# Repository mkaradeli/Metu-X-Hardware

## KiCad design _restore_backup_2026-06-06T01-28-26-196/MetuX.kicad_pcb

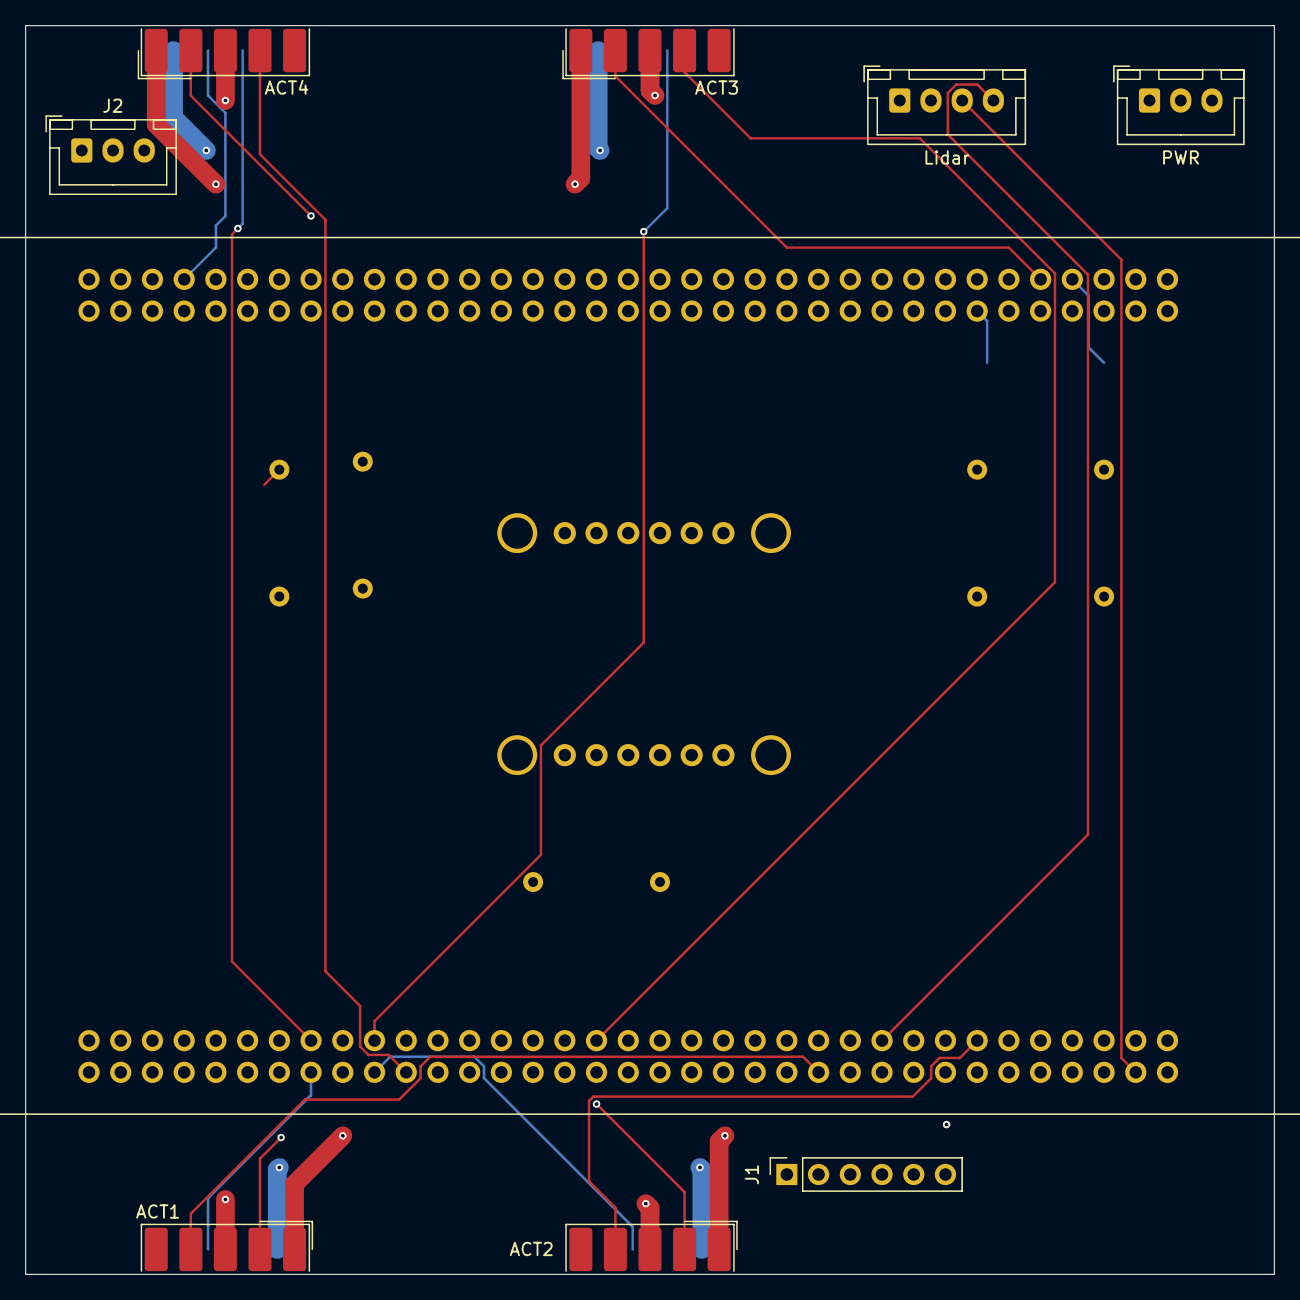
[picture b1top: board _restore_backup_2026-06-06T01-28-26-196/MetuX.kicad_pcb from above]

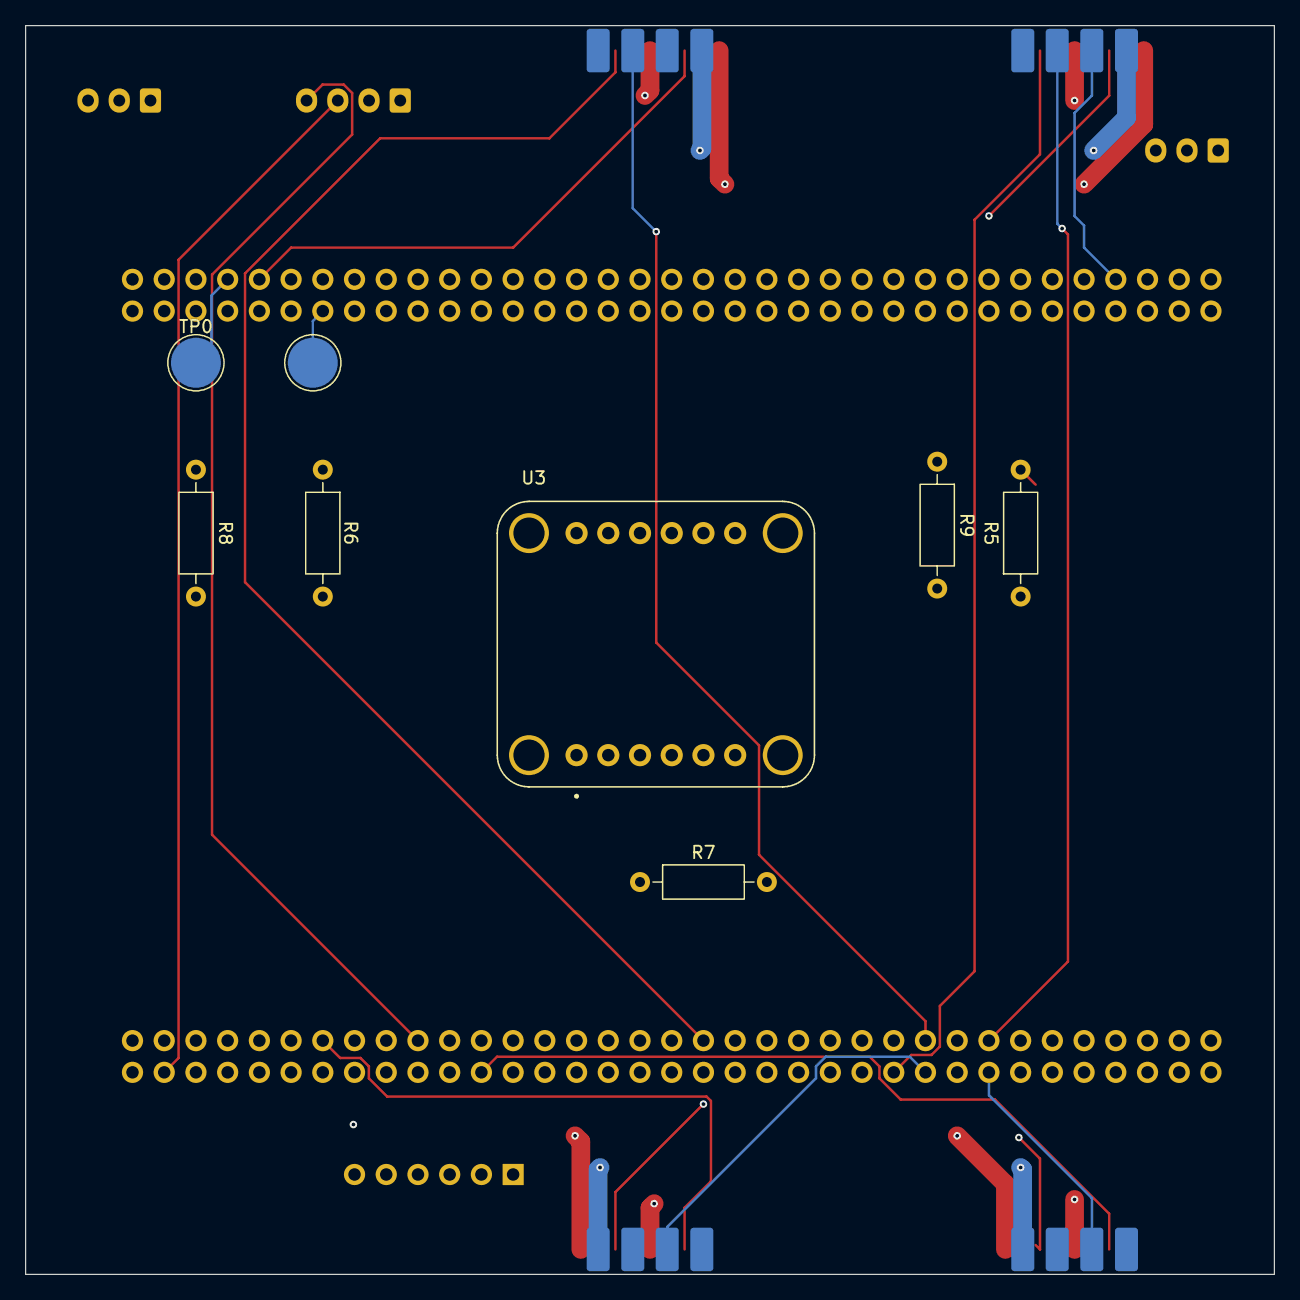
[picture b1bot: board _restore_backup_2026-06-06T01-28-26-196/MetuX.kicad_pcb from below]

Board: 4 copper layers, 100.0 x 100.0 mm, 17 parts (8 on the bottom side), 38 nets.

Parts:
ACT1, ACT2, ACT3, ACT4: DE9_Socket; DSUB-9_Socket_EdgeMount_P2.77mm
J1: SD_Card_Breakout; PinSocket_1x06_P2.54mm_Vertical
J2: Manifold; JST_XH_B3B-XH-A_1x03_P2.50mm_Vertical
J3: PWR; JST_XH_B3B-XH-A_1x03_P2.50mm_Vertical
J4: Lidar; JST_XH_B4B-XH-A_1x04_P2.50mm_Vertical
R5, R6, R7, R8, R9: 150R; R_Axial_DIN0207_L6.3mm_D2.5mm_P10.16mm_Horizontal
TP0: ~{BOOT0}; TestPoint_Pad_D4.0mm
TP1: NRST; TestPoint_Pad_D4.0mm
U2: NUCLEO144-H755ZI-Q
U3: 4754; MODULE_4754

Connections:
+5V: ACT1.1, ACT2.1, ACT3.1, ACT4.1, J1.5 (VCC), J3.1, J4.2, U2.CN11_6 (E5V), U3.JP1_1 (VIN)
+12V: ACT1.6, ACT2.6, ACT3.6, ACT4.6, J2.3, J3.3
/CS0: ACT1.4, U2.CN12_24 (PB1)
/CS1: ACT2.4, U2.CN12_13 (PA6)
/CS2: ACT3.4, U2.CN12_37 (PA3)
/CS3: ACT4.4, U2.CN12_50 (PF14)
/HE0: ACT1.5, U2.CN11_38 (PC0)
/HE1: ACT2.5, U2.CN11_32 (PA4)
/HE2: ACT3.5, U2.CN11_28 (PA0)
/HE3: ACT4.5, U2.CN12_11 (PA5)
/IMU_SCL: U2.CN12_17 (PB6), U3.JP1_4 (SCL)
/IMU_SDA: U2.CN11_21 (LD2/PB7), U3.JP1_5 (SDA)
/LIDAR_UART_RX: J4.4, U2.CN12_19 (PC7)
/LIDAR_UART_TX: J4.3, U2.CN12_4 (PC6)
/L_EN_0: ACT1.9, U2.CN12_47 (PE10)
/L_EN_1: ACT2.9, U2.CN12_53 (PE15)
/L_EN_2: ACT3.9, U2.CN12_18 (PB11)
/L_EN_3: ACT4.9, U2.CN12_44 (PE7)
/PT0: ACT1.2, R5.2, U2.CN11_56 (PF9)
/PT1: ACT2.2, R7.2, U2.CN12_42 (PF10)
/PT2: ACT3.2, R8.1, U2.CN11_9 (PF6)
/PT3: ACT4.2, R6.1, U2.CN11_11 (PF7)
/PT4: J2.1, R9.1, U2.CN11_54 (PF8)
/PWM_0: ACT1.8, U2.CN12_56 (PE11)
/PWM_1: ACT2.8, U2.CN12_52 (PE9)
/PWM_2: ACT3.8, U2.CN12_51 (PE14)
/PWM_3: ACT4.8, U2.CN12_55 (PE13)
/R_EN_0: ACT1.7, U2.CN12_49 (PE12)
/R_EN_1: ACT2.7, U2.CN12_60 (PF15)
/R_EN_2: ACT3.7, U2.CN12_40 (PE8)
/R_EN_3: ACT4.7, U2.CN11_63 (PG9)
/SD_CS: J1.1 (CS), U2.CN12_25 (PB10)
/SD_MISO: J1.4 (MISO), U2.CN12_27 (PB4)
/SD_MOSI: J1.3 (MOSI), U2.CN12_29 (PB5)
/SD_SCK: J1.2 (SCK), U2.CN12_31 (SWO/PB3)
GND: ACT1.3, ACT2.3, ACT3.3, ACT4.3, J1.6 (GND), J3.2, J4.1, R5.1, R6.2, R7.1, R8.2, R9.2, U2.CN11_8 (GND), U2.CN11_19 (GND), U2.CN11_20 (GND), U2.CN11_22 (GND), U2.CN11_49 (GND), U2.CN11_60 (GND), U2.CN12_9 (GND), U2.CN12_20 (GND), U2.CN12_32 (AGND), U2.CN12_39 (GND), U2.CN12_54 (GND), U2.CN12_63 (GND), U3.JP1_3 (GND)
unnamed: TP0.1 (1_1), U2.CN11_7 (~BOOT0)
unnamed: TP1.1 (1_1), U2.CN11_14 (~RST)

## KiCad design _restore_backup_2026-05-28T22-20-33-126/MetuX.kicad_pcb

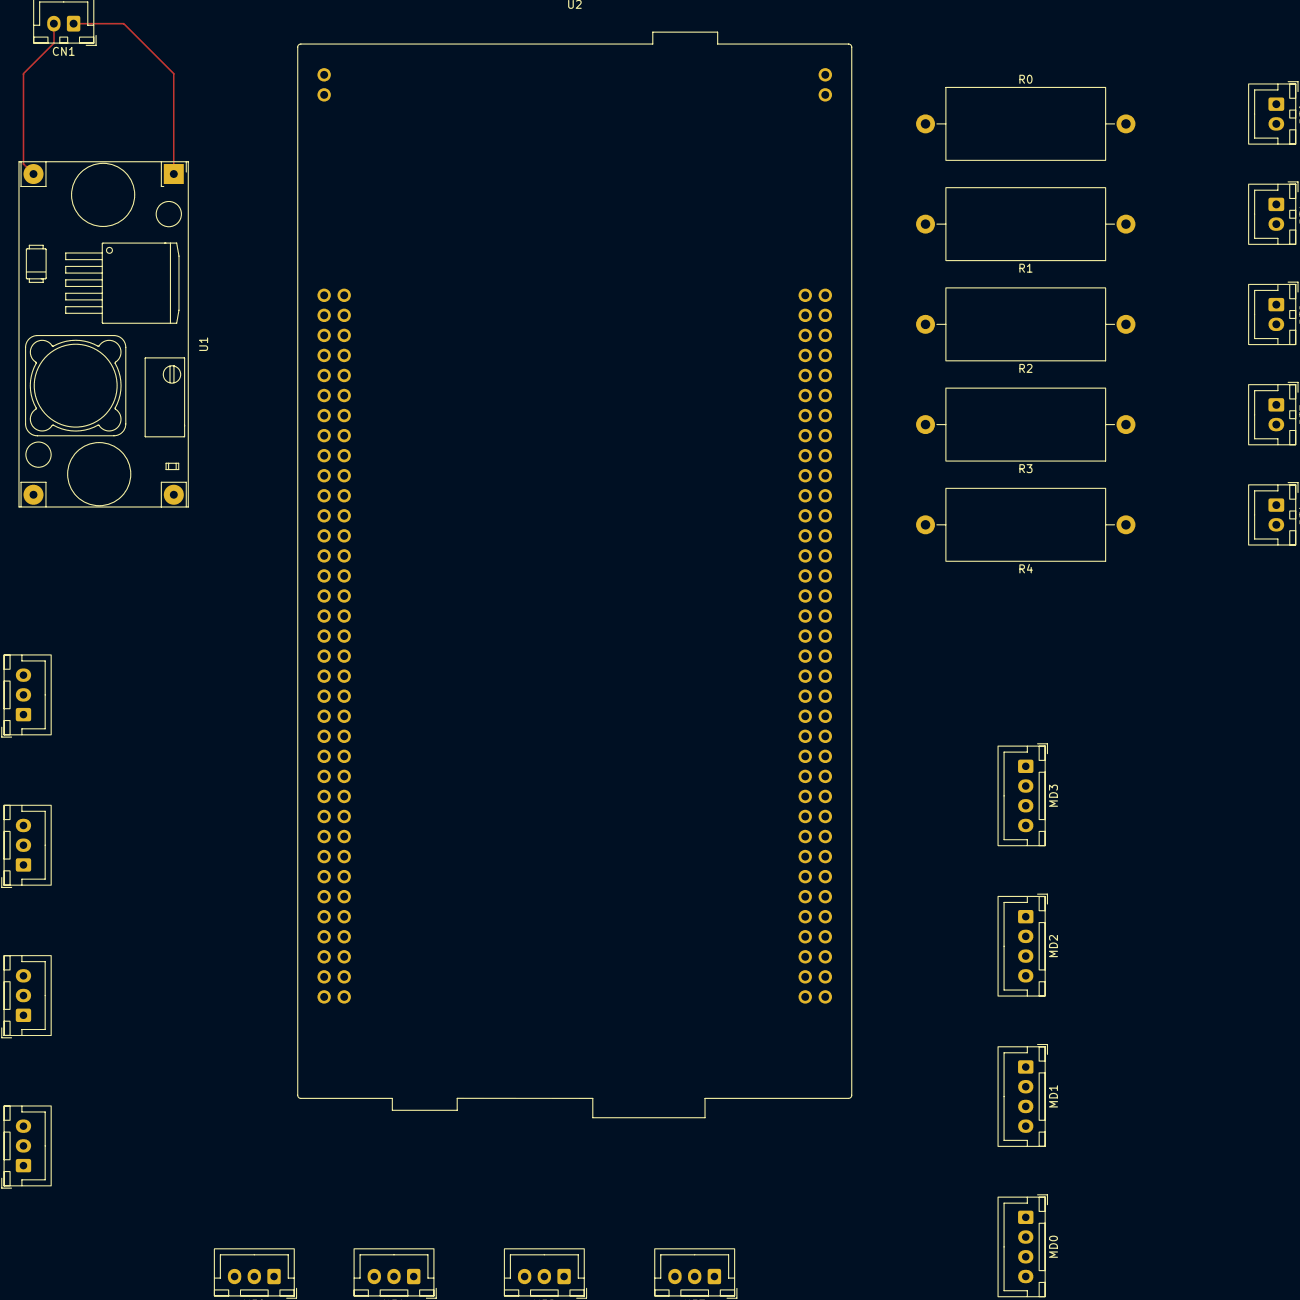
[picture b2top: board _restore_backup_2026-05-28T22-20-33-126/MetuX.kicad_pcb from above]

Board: 2 copper layers, 25 parts (0 on the bottom side), 8 nets.

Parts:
CN1: Conn_01x02_Socket; JST_XH_B2B-XH-A_1x02_P2.50mm_Vertical
CS0, CS1, CS2, CS3: Conn_01x03_Socket; JST_XH_B3B-XH-A_1x03_P2.50mm_Vertical
HE0, HE1, HE2, HE3: Conn_01x03_Socket; JST_XH_B3B-XH-A_1x03_P2.50mm_Vertical
MD0, MD1, MD2, MD3: Conn_01x04_Socket; JST_XH_B4B-XH-A_1x04_P2.50mm_Vertical
PT0, PT1, PT2, PT3, PT4: Conn_01x02_Socket; JST_XH_B2B-XH-A_1x02_P2.50mm_Vertical
R0, R1, R2, R3, R4: 150R; R_Axial_DIN0922_L20.0mm_D9.0mm_P25.40mm_Horizontal
U1: YAAJ_DCDC_StepDown_LM2596
U2: NUCLEO144-H743ZI; ST_Morpho_Connector_144_STLink

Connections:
+5V: CS0.1, CS1.1, CS2.1, CS3.1, HE0.1, HE1.1, HE2.1, HE3.1, U1.4 (Vout)
+12V: CN1.1, PT0.1, PT1.1, PT2.1, PT3.1, PT4.1, U1.1 (Vin)
/Basınç Sensörleri/PT0: PT0.2, R0.2
/Basınç Sensörleri/PT1: PT1.2, R1.1
/Basınç Sensörleri/PT2: PT2.2, R2.1
/Basınç Sensörleri/PT3: PT3.2, R3.1
/Basınç Sensörleri/PT4: PT4.2, R4.1
GND: CN1.2, CS0.3, CS1.3, CS2.3, CS3.3, HE0.3, HE1.3, HE2.3, HE3.3, MD0.1, MD1.1, MD2.1, MD3.1, R0.1, R1.2, R2.2, R3.2, R4.2, U1.2 (GND), U1.3 (GND), U2.19 (GND_19)

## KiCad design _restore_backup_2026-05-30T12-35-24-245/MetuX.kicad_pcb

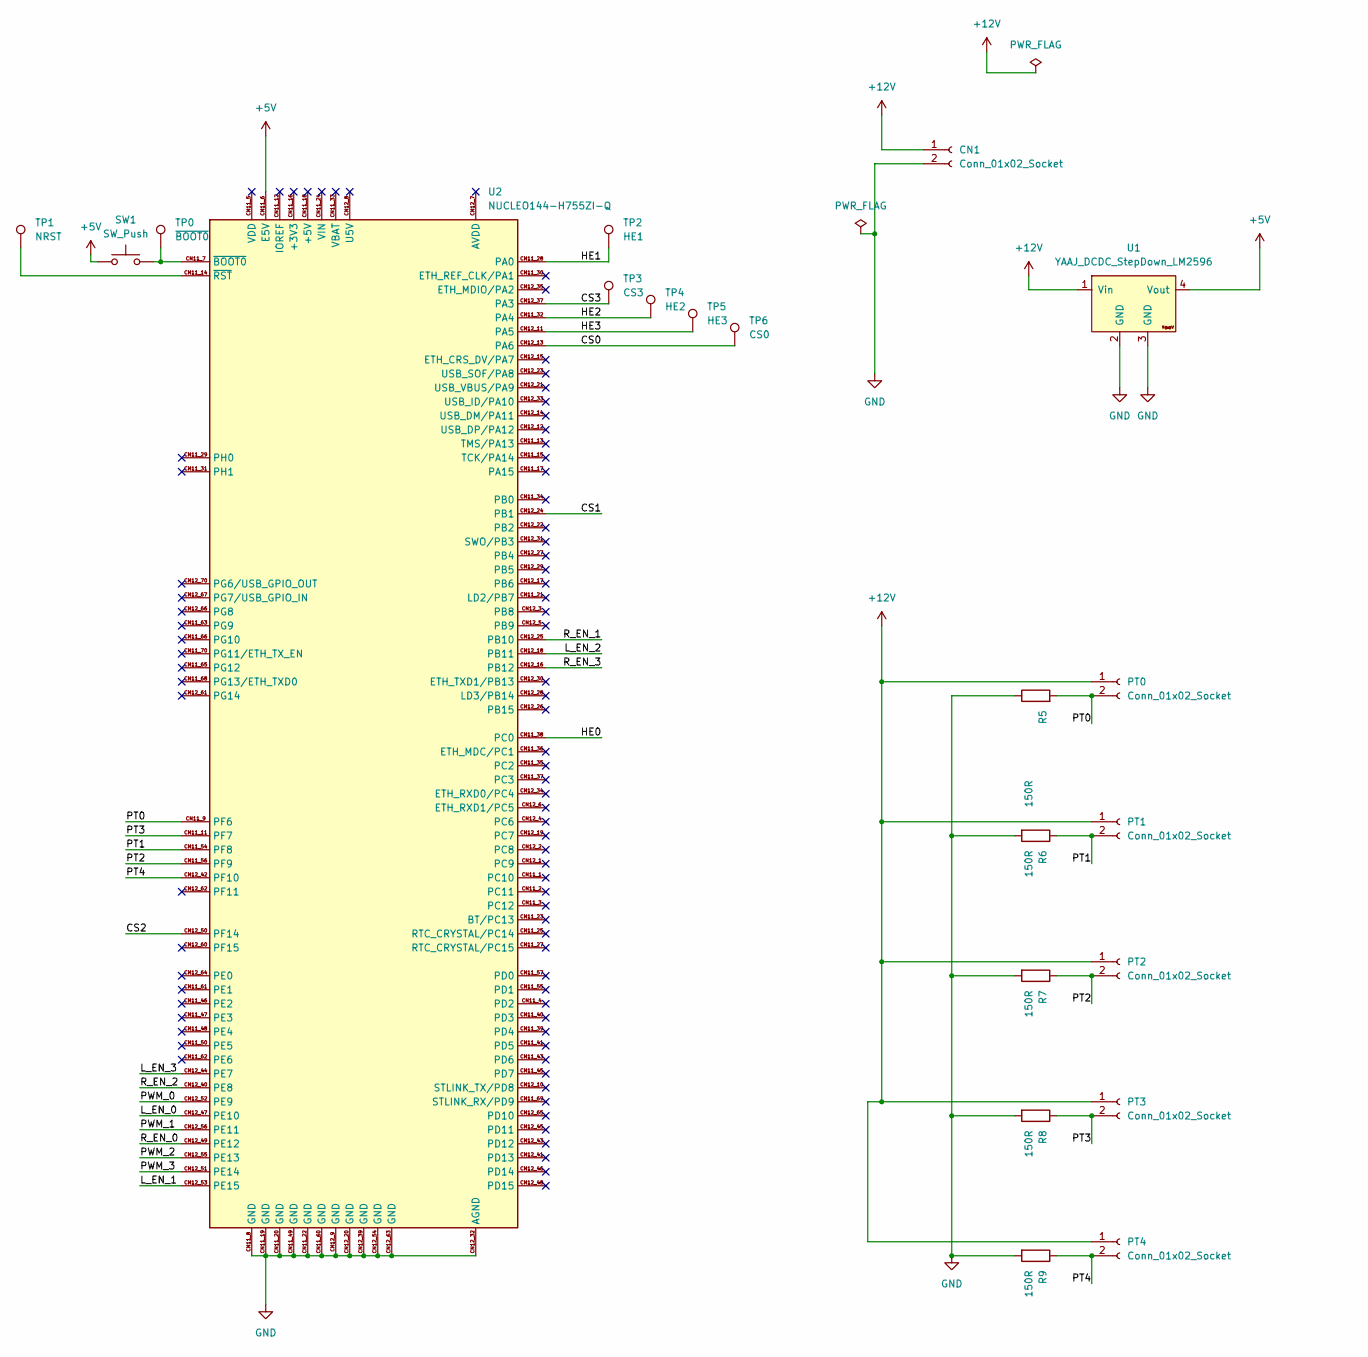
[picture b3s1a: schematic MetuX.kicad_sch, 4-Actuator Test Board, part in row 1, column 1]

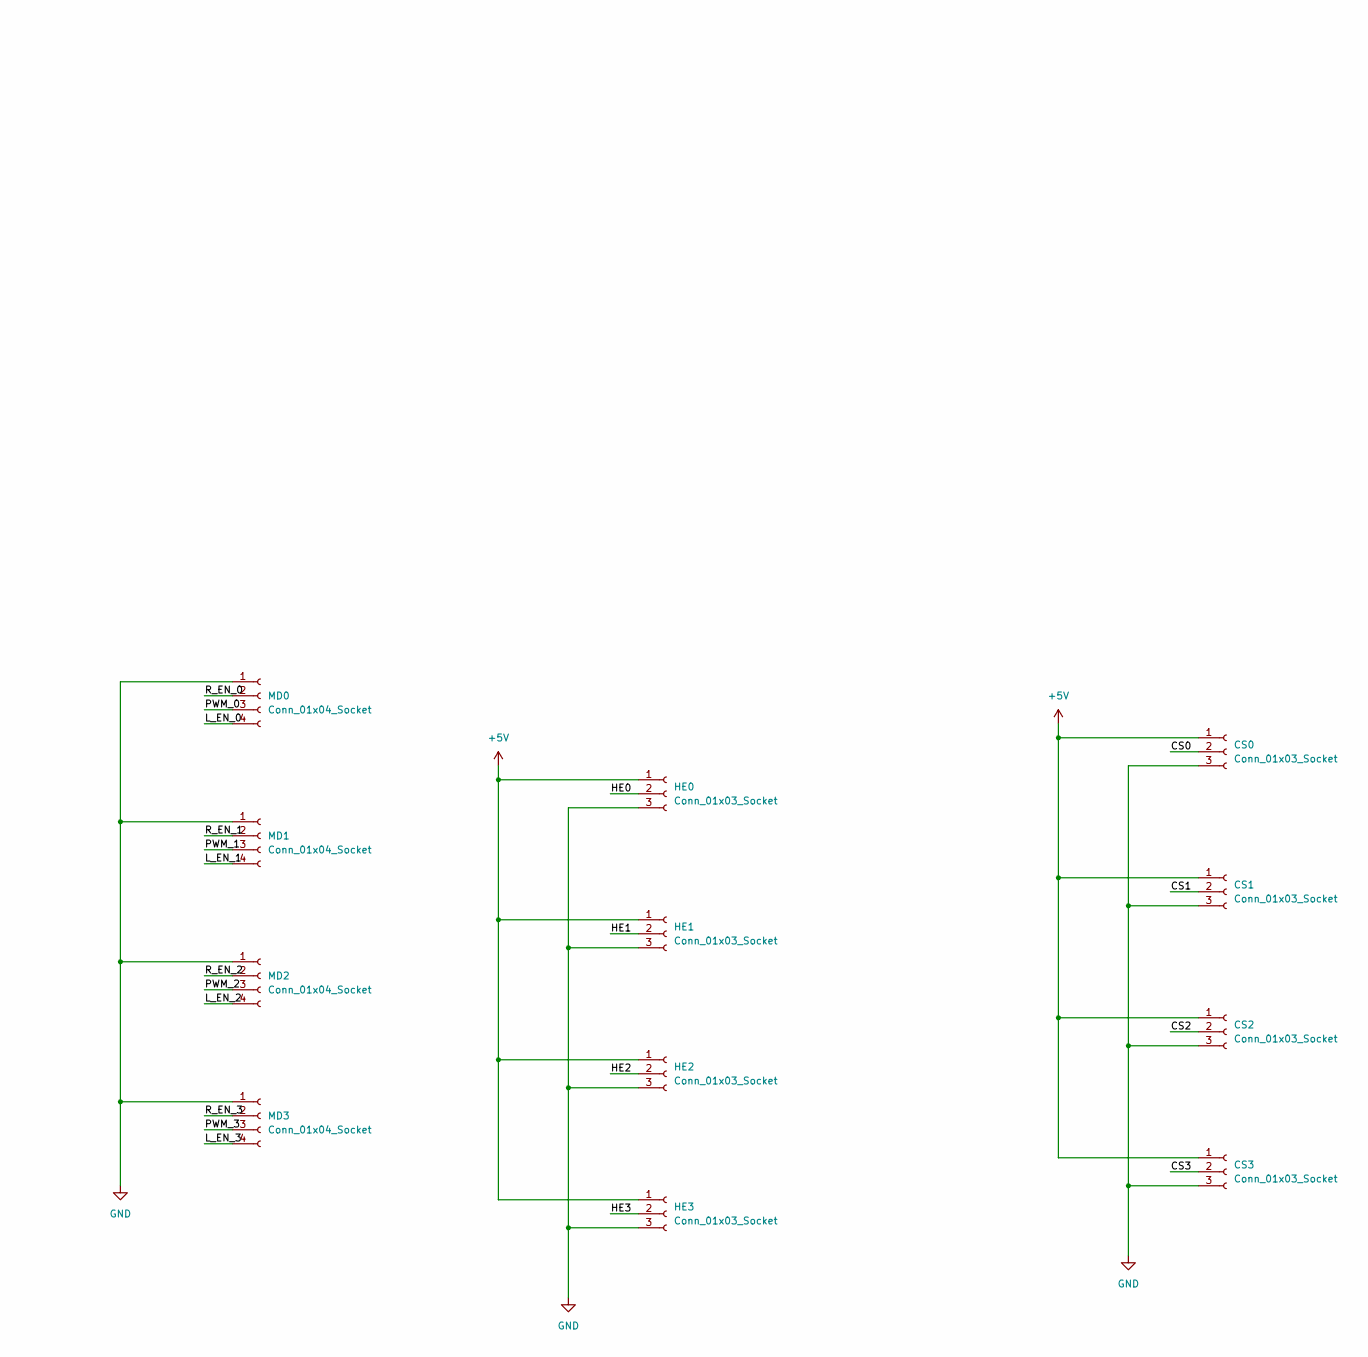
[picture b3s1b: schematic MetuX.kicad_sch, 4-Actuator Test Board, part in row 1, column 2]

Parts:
CN1: Conn_01x02_Socket; JST_XH_B2B-XH-A_1x02_P2.50mm_Vertical
CS0, CS1, CS2, CS3: Conn_01x03_Socket; JST_XH_B3B-XH-A_1x03_P2.50mm_Vertical
HE0, HE1, HE2, HE3: Conn_01x03_Socket; JST_XH_B3B-XH-A_1x03_P2.50mm_Vertical
MD0, MD1, MD2, MD3: Conn_01x04_Socket; JST_XH_B4B-XH-A_1x04_P2.50mm_Vertical
PT0, PT1, PT2, PT3, PT4: Conn_01x02_Socket; JST_XH_B2B-XH-A_1x02_P2.50mm_Vertical
R5, R6, R7, R8, R9: 150R; R_Axial_DIN0207_L6.3mm_D2.5mm_P10.16mm_Horizontal
SW1: SW_Push; SW_PUSH_6mm_H4.3mm
TP0: ~{BOOT0}; TestPoint_Pad_D4.0mm
TP1: NRST; TestPoint_Pad_D4.0mm
TP2: HE1; TestPoint_Pad_D4.0mm
TP3: CS3; TestPoint_Pad_D4.0mm
TP4: HE2; TestPoint_Pad_D4.0mm
TP5: HE3; TestPoint_Pad_D4.0mm
TP6: CS0; TestPoint_Pad_D4.0mm
U1: YAAJ_DCDC_StepDown_LM2596
U2: NUCLEO144-H755ZI-Q

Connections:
+5V: CS0.1, CS1.1, CS2.1, CS3.1, HE0.1, HE1.1, HE2.1, HE3.1, SW1.1, U1.4 (Vout), U2.CN11_6 (E5V)
+12V: CN1.1, PT0.1, PT1.1, PT2.1, PT3.1, PT4.1, U1.1 (Vin)
/CS0: CS0.2, TP6.1 (1_1), U2.CN12_13 (PA6)
/CS1: CS1.2, U2.CN12_24 (PB1)
/CS2: CS2.2, U2.CN12_50 (PF14)
/CS3: CS3.2, TP3.1 (1_1), U2.CN12_37 (PA3)
/HE0: HE0.2, U2.CN11_38 (PC0)
/HE1: HE1.2, TP2.1 (1_1), U2.CN11_28 (PA0)
/HE2: HE2.2, TP4.1 (1_1), U2.CN11_32 (PA4)
/HE3: HE3.2, TP5.1 (1_1), U2.CN12_11 (PA5)
/L_EN_0: MD0.4, U2.CN12_47 (PE10)
/L_EN_1: MD1.4, U2.CN12_53 (PE15)
/L_EN_2: MD2.4, U2.CN12_18 (PB11)
/L_EN_3: MD3.4, U2.CN12_44 (PE7)
/PT0: PT0.2, R5.2, U2.CN11_9 (PF6)
/PT1: PT1.2, R6.1, U2.CN11_54 (PF8)
/PT2: PT2.2, R7.1, U2.CN11_56 (PF9)
/PT3: PT3.2, R8.1, U2.CN11_11 (PF7)
/PT4: PT4.2, R9.1, U2.CN12_42 (PF10)
/PWM_0: MD0.3, U2.CN12_52 (PE9)
/PWM_1: MD1.3, U2.CN12_56 (PE11)
/PWM_2: MD2.3, U2.CN12_55 (PE13)
/PWM_3: MD3.3, U2.CN12_51 (PE14)
/R_EN_0: MD0.2, U2.CN12_49 (PE12)
/R_EN_1: MD1.2, U2.CN12_25 (PB10)
/R_EN_2: MD2.2, U2.CN12_40 (PE8)
/R_EN_3: MD3.2, U2.CN12_16 (PB12)
GND: CN1.2, CS0.3, CS1.3, CS2.3, CS3.3, HE0.3, HE1.3, HE2.3, HE3.3, MD0.1, MD1.1, MD2.1, MD3.1, R5.1, R6.2, R7.2, R8.2, R9.2, U1.2 (GND), U1.3 (GND), U2.CN11_8 (GND), U2.CN11_19 (GND), U2.CN11_20 (GND), U2.CN11_22 (GND), U2.CN11_49 (GND), U2.CN11_60 (GND), U2.CN12_9 (GND), U2.CN12_20 (GND), U2.CN12_32 (AGND), U2.CN12_39 (GND), U2.CN12_54 (GND), U2.CN12_63 (GND)
unnamed: SW1.2, TP0.1 (1_1), U2.CN11_7 (~BOOT0)
unnamed: TP1.1 (1_1), U2.CN11_14 (~RST)

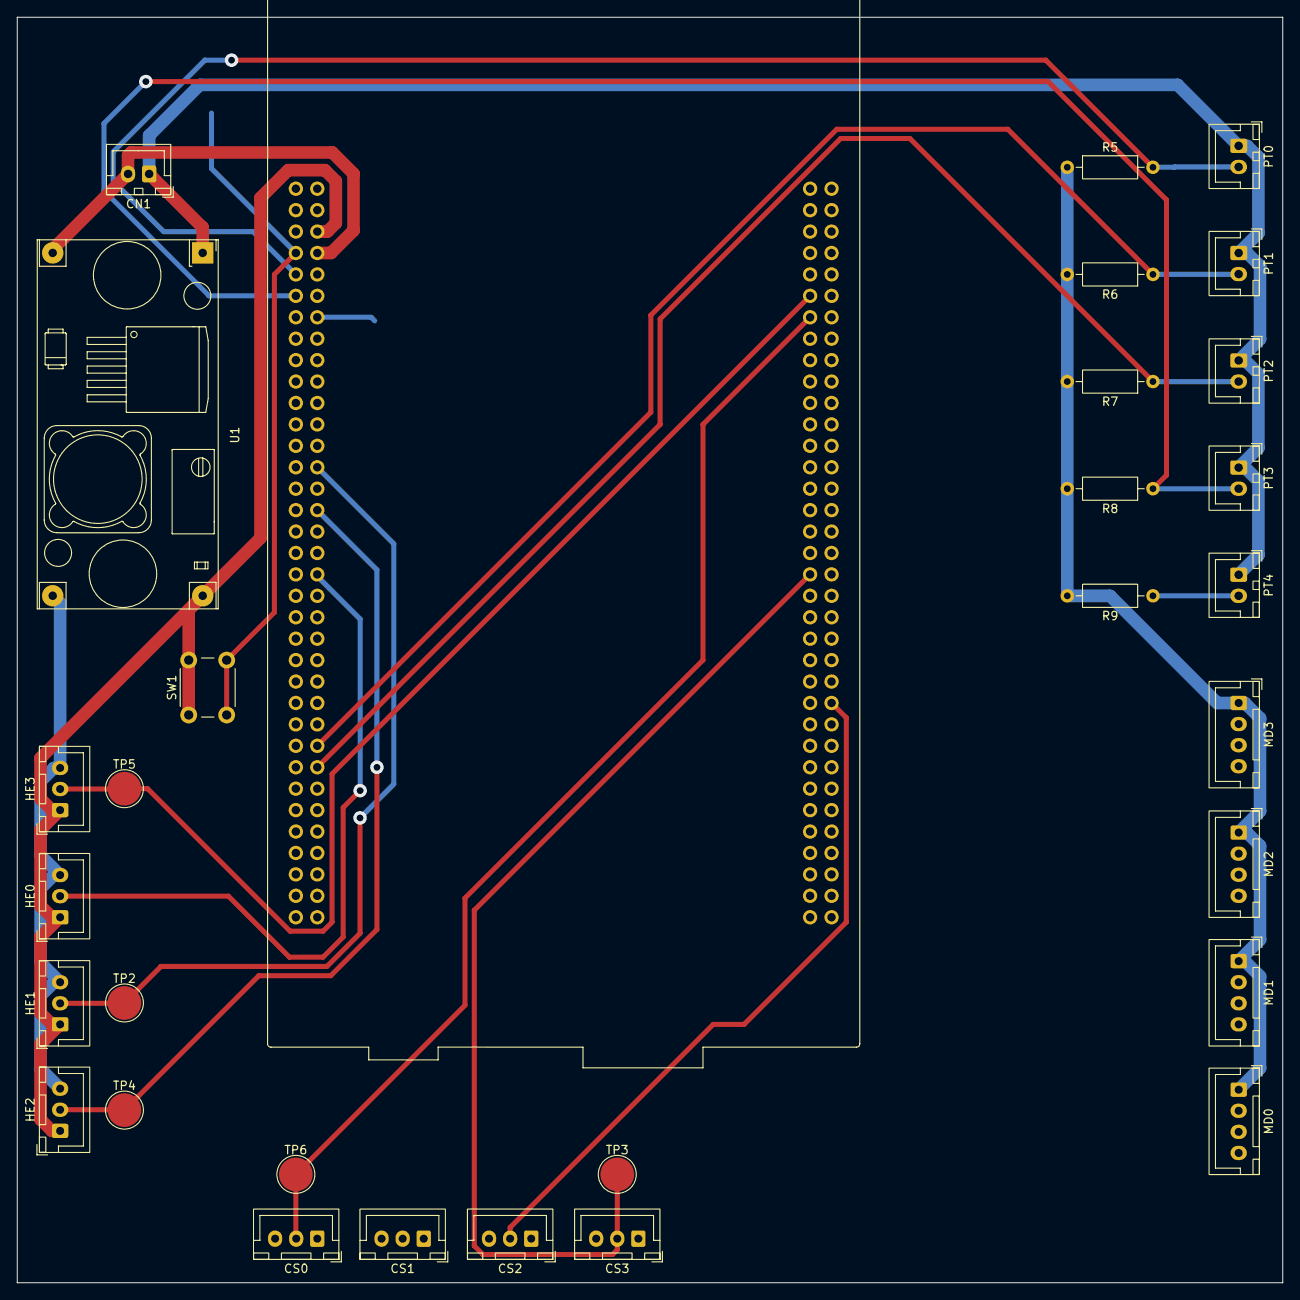
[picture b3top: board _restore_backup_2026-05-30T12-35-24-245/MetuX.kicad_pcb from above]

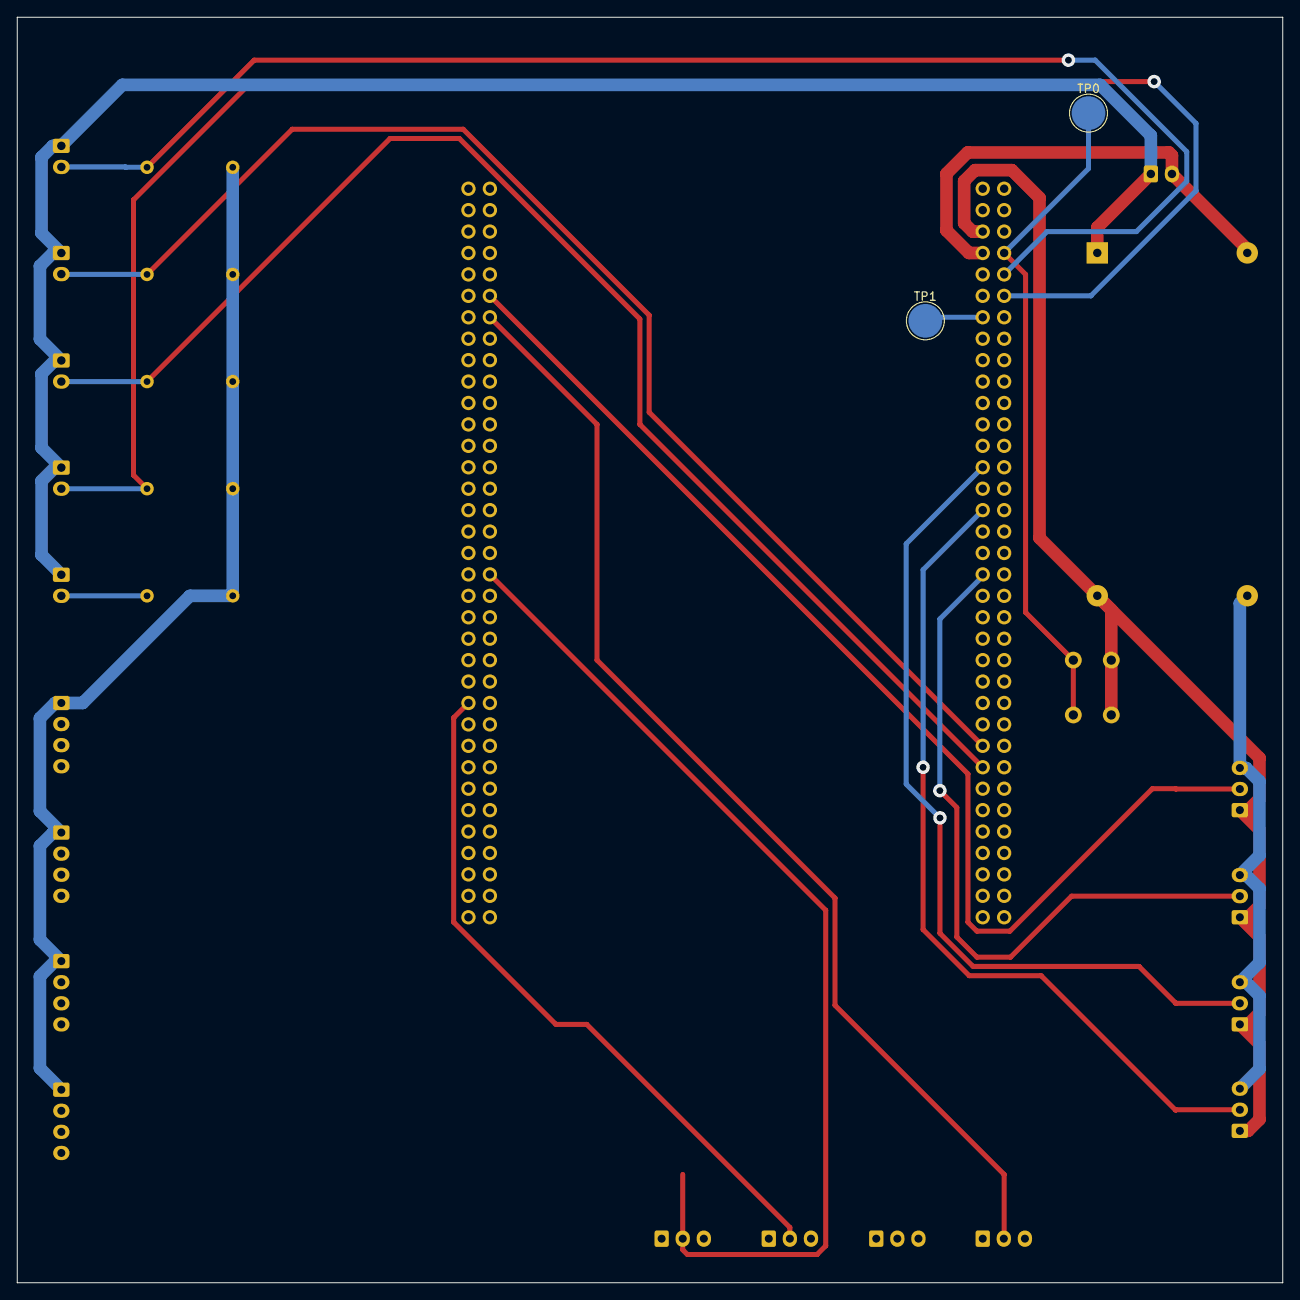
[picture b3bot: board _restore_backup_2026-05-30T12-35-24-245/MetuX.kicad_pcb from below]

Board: 2 copper layers, 150.0 x 150.0 mm, 33 parts (2 on the bottom side), 30 nets.
